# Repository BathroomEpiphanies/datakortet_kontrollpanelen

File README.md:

# datakortet_kontrollpanelen
Källkod för datakortets kontrollpanelen

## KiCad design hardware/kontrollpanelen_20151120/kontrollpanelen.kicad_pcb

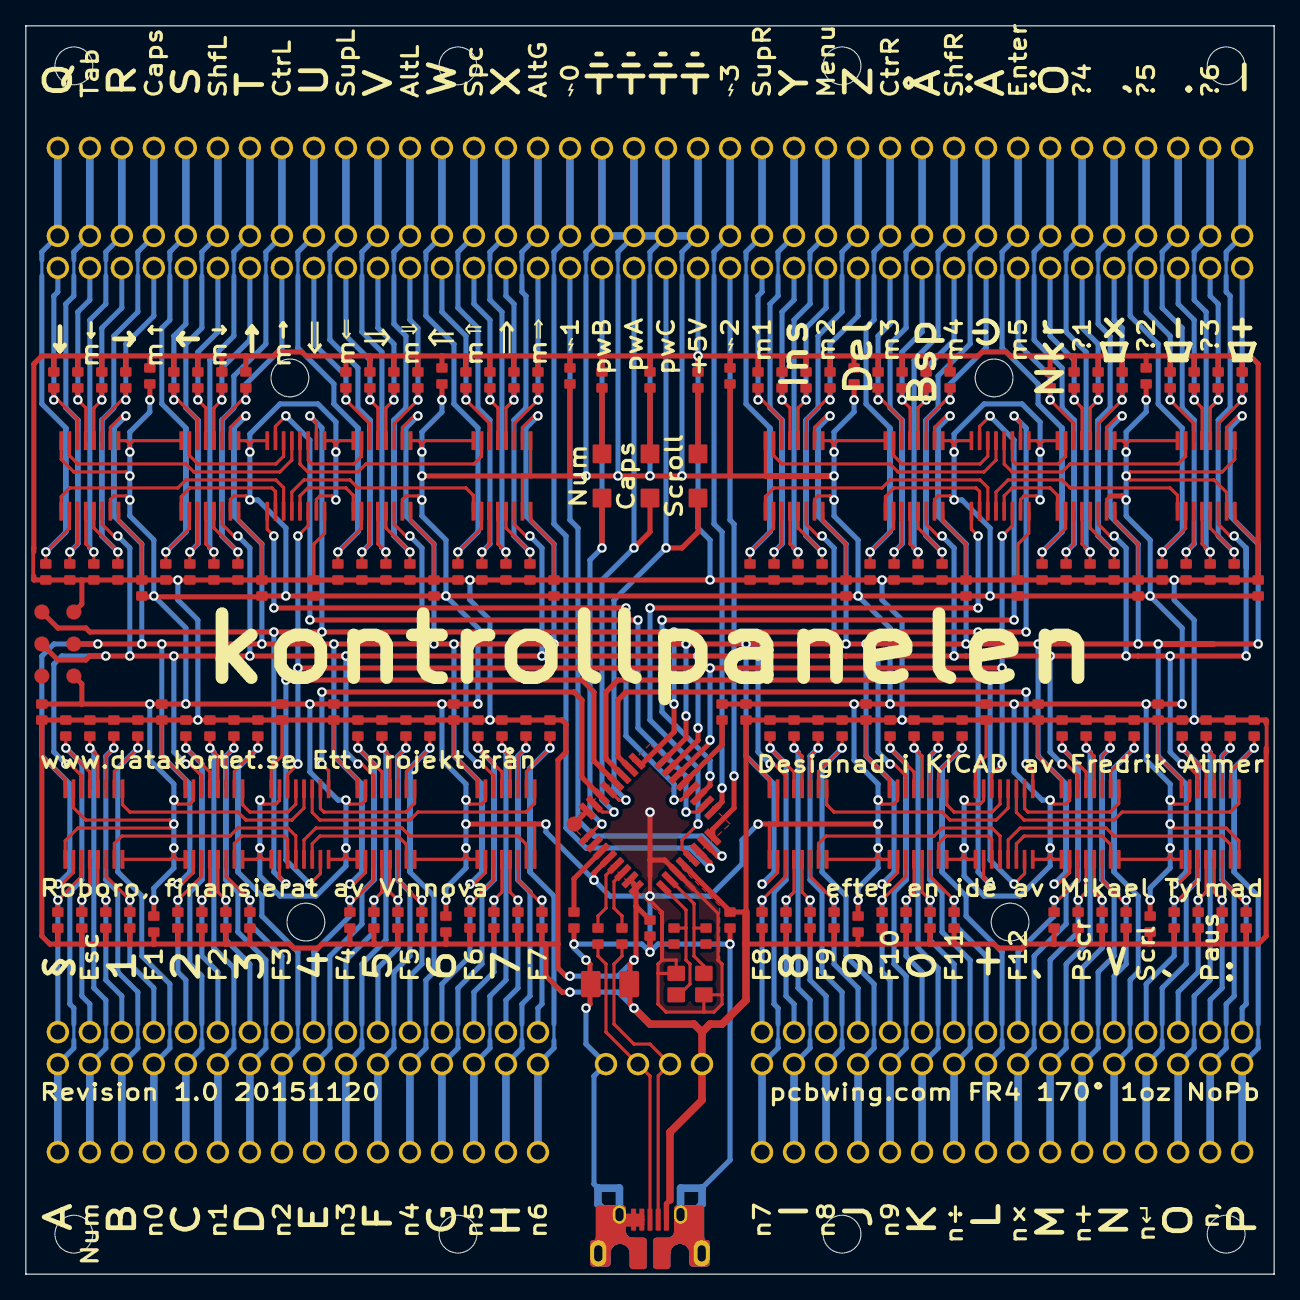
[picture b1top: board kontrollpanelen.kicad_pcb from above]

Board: 2 copper layers, 99.1 x 99.1 mm, 204 parts (0 on the bottom side), 192 nets.

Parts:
ANY1: ANYTHING; Kontrollpanelen
C1, C2, C3, C4, C5, C6, C7, C8, C9, C10, C11, C12, C13, C14, C15, C16, C17, C18, C19, C20, C301, C302, C303, C304, C305, C306, C307, C308, C309, C310: 0.1µ; Resistor_0603_-_Panasonic_ERJ
C21, C204: 1µF; Resistor_0603_-_Panasonic_ERJ
C201: 0.1µF; Resistor_0603_-_Panasonic_ERJ
C202, C203: 18pF; Resistor_0603_-_Panasonic_ERJ
C205: 10μF; Capacitor_1206_-_Vishay
D201, D202, D203: LED; LED_32x16mm_-_Avago_HSMx-C150
J1, J2, J3, J4: Terminal; Screw_Terminal_32
J5: USB_5; Connector_USBmicroB_inverted_-_FCI
J6: Terminal_12; Screw_Terminal_12
J7: ISP6; ISP_SMD_6
J8: USB_4; Screw_Terminal_4
R1, R2, R3, R4, R5, R6, R7, R8, R9, R10, R11, R12, R13, R14, R15, R16, R17, R18, R19, R20, R21, R22, R23, R24, R25, R26, R27, R28, R29, R30, R31, R32, R33, R34, R35, R36, R37, R38, R39, R40, R41, R42, R43, R44, R45, R46, R47, R48, R49, R50, R51, R52, R53, R54, R55, R56, R57, R58, R59, R60, R61, R62, R63, R64, R65, R66, R67, R68, R69, R70, R71, R72, R73, R74, R75, R76, R77, R78, R79, R80, R81, R82, R83, R84, R85, R86, R87, R88, R89, R90, R91, R92, R93, R94, R95, R96, R97, R98, R99, R100, R101, R102, R103, R104, R105, R106, R107, R108, R109, R110, R111, R112, R113, R114, R115, R116, R117, R118, R119, R120, R121, R122, R123, R124, R125, R126, R127, R128: 22MΩ; Resistor_0603_-_Panasonic_ERJ
R201, R204, R205, R206: 10kΩ; Resistor_0603_-_Panasonic_ERJ
R202, R203: 22Ω; Resistor_0603_-_Panasonic_ERJ
U1, U2, U3, U4, U5, U6, U7, U8, U9, U10, U11, U12, U13, U14, U15, U16, U17, U18, U19, U20: 74HC153; TSSOP16_-_Texas_Instruments
U201: ATMEGA32U2; TQFP32_-_Atmel
X201: 16MHz; Crystal_32x25mm_-_Abracon_ABM10

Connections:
/INT0: J6.1, U201.6
/INT1: J6.2, U201.7
/INT2: J6.12, U201.8
/INT3: J6.11, U201.9
/PWMA: J6.6, U201.23
/PWMB: J6.4, U201.25
/PWMC: J6.8, U201.21
/S0: J7.3, U1.14, U2.14, U3.14, U4.14, U5.14, U6.14, U7.14, U8.14, U9.14, U10.14, U11.14, U12.14, U13.14, U14.14, U15.14, U16.14, U201.15
/S1: J7.4, U1.2, U2.2, U3.2, U4.2, U5.2, U6.2, U7.2, U8.2, U9.2, U10.2, U11.2, U12.2, U13.2, U14.2, U15.2, U16.2, U201.16
/S2: U17.14, U18.14, U19.14, U20.14, U201.14
/S3: J7.1, U17.2, U18.2, U19.2, U20.2, U201.17
/Y0: U19.9, U201.22
/Y1: U19.7, U201.20
/Y2: U20.9, U201.18
/Y3: U20.7, U201.19
/Y4: U18.9, U201.5
/Y5: U18.7, U201.11
/Y6: U17.9, U201.12
/Y7: U17.7, U201.10
GND: C1.2, C2.2, C3.2, C4.2, C5.2, C6.2, C7.2, C8.2, C9.2, C10.2, C11.2, C12.2, C13.2, C14.2, C15.2, C16.2, C17.2, C18.2, C19.2, C20.2, C21.2, C201.2, C202.2, C203.2, C204.2, C205.2, C301.2, C302.2, C303.2, C304.2, C305.2, C306.2, C307.2, C308.2, C309.2, C310.2, J5.4, J5.5, J6.3, J6.5, J6.7, J6.9, J7.6, J8.4, R201.2, U1.1, U1.8, U1.15, U2.1, U2.8, U2.15, U3.1, U3.8, U3.15, U4.1, U4.8, U4.15, U5.1, U5.8, U5.15, U6.1, U6.8, U6.15, U7.1, U7.8, U7.15, U8.1, U8.8, U8.15, U9.1, U9.8, U9.15, U10.1, U10.8, U10.15, U11.1, U11.8, U11.15, U12.1, U12.8, U12.15, U13.1, U13.8, U13.15, U14.1, U14.8, U14.15, U15.1, U15.8, U15.15, U16.1, U16.8, U16.15, U17.1, U17.8, U17.15, U18.1, U18.8, U18.15, U19.1, U19.8, U19.15, U20.1, U20.8, U20.15, U201.3, U201.28, X201.2, X201.4
unnamed: C21.1, U201.27
unnamed: C202.1, U201.2, X201.3
unnamed: C203.1, U201.1, X201.1
unnamed: D201.1, R204.1
unnamed: D202.1, R205.1
unnamed: D203.1, R206.1
unnamed: J1.1, R33.1, U1.10
unnamed: J1.2, R1.1, U1.6
unnamed: J1.3, R34.1, U1.11
unnamed: J1.4, R2.1, U1.5
unnamed: J1.5, R35.1, U1.12
unnamed: J1.6, R3.1, U1.4
unnamed: J1.7, R36.1, U1.13
unnamed: J1.8, R4.1, U1.3
unnamed: J1.9, R37.1, U2.10
unnamed: J1.10, R5.1, U2.6
unnamed: J1.11, R38.1, U2.11
unnamed: J1.12, R6.1, U2.5
unnamed: J1.13, R39.1, U2.12
unnamed: J1.14, R7.1, U2.4
unnamed: J1.15, R40.1, U2.13
unnamed: J1.16, R8.1, U2.3
unnamed: J1.17, R41.1, U3.10
unnamed: J1.18, R9.1, U3.6
unnamed: J1.19, R42.1, U3.11
unnamed: J1.20, R10.1, U3.5
unnamed: J1.21, R43.1, U3.12
unnamed: J1.22, R11.1, U3.4
unnamed: J1.23, R44.1, U3.13
unnamed: J1.24, R12.1, U3.3
unnamed: J1.25, R45.1, U4.10
unnamed: J1.26, R13.1, U4.6
unnamed: J1.27, R46.1, U4.11
unnamed: J1.28, R14.1, U4.5
unnamed: J1.29, R47.1, U4.12
unnamed: J1.30, R15.1, U4.4
unnamed: J1.31, R48.1, U4.13
unnamed: J1.32, R16.1, U4.3
unnamed: J2.1, R49.1, U5.10
unnamed: J2.2, R17.1, U5.6
unnamed: J2.3, R50.1, U5.11
unnamed: J2.4, R18.1, U5.5
unnamed: J2.5, R51.1, U5.12
unnamed: J2.6, R19.1, U5.4
unnamed: J2.7, R52.1, U5.13
unnamed: J2.8, R20.1, U5.3
unnamed: J2.9, R53.1, U6.10
unnamed: J2.10, R21.1, U6.6
unnamed: J2.11, R54.1, U6.11
unnamed: J2.12, R22.1, U6.5
unnamed: J2.13, R55.1, U6.12
unnamed: J2.14, R23.1, U6.4
unnamed: J2.15, R56.1, U6.13
unnamed: J2.16, R24.1, U6.3
unnamed: J2.17, R57.1, U7.10
unnamed: J2.18, R25.1, U7.6
unnamed: J2.19, R58.1, U7.11
unnamed: J2.20, R26.1, U7.5
unnamed: J2.21, R59.1, U7.12
unnamed: J2.22, R27.1, U7.4
unnamed: J2.23, R60.1, U7.13
unnamed: J2.24, R28.1, U7.3
unnamed: J2.25, R61.1, U8.10
unnamed: J2.26, R29.1, U8.6
unnamed: J2.27, R62.1, U8.11
unnamed: J2.28, R30.1, U8.5
unnamed: J2.29, R63.1, U8.12
unnamed: J2.30, R31.1, U8.4
unnamed: J2.31, R64.1, U8.13
unnamed: J2.32, R32.1, U8.3
unnamed: J3.1, R80.1, U12.10
unnamed: J3.2, R112.1, U12.6
unnamed: J3.3, R79.1, U12.11
unnamed: J3.4, R111.1, U12.5
unnamed: J3.5, R78.1, U12.12
unnamed: J3.6, R110.1, U12.4
unnamed: J3.7, R77.1, U12.13
unnamed: J3.8, R109.1, U12.3
unnamed: J3.9, R76.1, U11.10
unnamed: J3.10, R108.1, U11.6
unnamed: J3.11, R75.1, U11.11
unnamed: J3.12, R107.1, U11.5
unnamed: J3.13, R74.1, U11.12
unnamed: J3.14, R106.1, U11.4
unnamed: J3.15, R73.1, U11.13
unnamed: J3.16, R105.1, U11.3
unnamed: J3.17, R72.1, U10.10
unnamed: J3.18, R104.1, U10.6
unnamed: J3.19, R71.1, U10.11
unnamed: J3.20, R103.1, U10.5
unnamed: J3.21, R70.1, U10.12
unnamed: J3.22, R102.1, U10.4
unnamed: J3.23, R69.1, U10.13
unnamed: J3.24, R101.1, U10.3
unnamed: J3.25, R68.1, U9.10
unnamed: J3.26, R100.1, U9.6
unnamed: J3.27, R67.1, U9.11
unnamed: J3.28, R99.1, U9.5
unnamed: J3.29, R66.1, U9.12
unnamed: J3.30, R98.1, U9.4
unnamed: J3.31, R65.1, U9.13
unnamed: J3.32, R97.1, U9.3
unnamed: J4.1, R96.1, U16.10
unnamed: J4.2, R128.1, U16.6
unnamed: J4.3, R95.1, U16.11
unnamed: J4.4, R127.1, U16.5
unnamed: J4.5, R94.1, U16.12
unnamed: J4.6, R126.1, U16.4
unnamed: J4.7, R93.1, U16.13
unnamed: J4.8, R125.1, U16.3
unnamed: J4.9, R92.1, U15.10
unnamed: J4.10, R124.1, U15.6
unnamed: J4.11, R91.1, U15.11
unnamed: J4.12, R123.1, U15.5
unnamed: J4.13, R90.1, U15.12
unnamed: J4.14, R122.1, U15.4
unnamed: J4.15, R89.1, U15.13
unnamed: J4.16, R121.1, U15.3
unnamed: J4.17, R88.1, U14.10
unnamed: J4.18, R120.1, U14.6
unnamed: J4.19, R87.1, U14.11
unnamed: J4.20, R119.1, U14.5
unnamed: J4.21, R86.1, U14.12
unnamed: J4.22, R118.1, U14.4
unnamed: J4.23, R85.1, U14.13
unnamed: J4.24, R117.1, U14.3
unnamed: J4.25, R84.1, U13.10
unnamed: J4.26, R116.1, U13.6
unnamed: J4.27, R83.1, U13.11
unnamed: J4.28, R115.1, U13.5
unnamed: J4.29, R82.1, U13.12
unnamed: J4.30, R114.1, U13.4
unnamed: J4.31, R81.1, U13.13
unnamed: J4.32, R113.1, U13.3
unnamed: J5.2, J8.2, R202.1
unnamed: J5.3, J8.3, R203.1
unnamed: R201.1, U201.13
unnamed: R202.2, U201.30
unnamed: R203.2, U201.29
unnamed: U1.7, U17.5
unnamed: U1.9, U17.11
unnamed: U10.7, U19.3
unnamed: U10.9, U19.13
unnamed: U11.7, U19.6
unnamed: U11.9, U19.10
unnamed: U12.7, U19.5
unnamed: U12.9, U19.11
unnamed: U13.7, U20.4
unnamed: U13.9, U20.12
unnamed: U14.7, U20.3
unnamed: U14.9, U20.13
unnamed: U15.7, U20.6
unnamed: U15.9, U20.10
unnamed: U16.7, U20.5
unnamed: U16.9, U20.11
unnamed: U3.7, U17.3
unnamed: U4.7, U17.4
unnamed: U2.7, U17.6
unnamed: U2.9, U17.10
unnamed: U4.9, U17.12
unnamed: U3.9, U17.13
unnamed: U7.7, U18.3
unnamed: U8.7, U18.4
unnamed: U5.7, U18.5
unnamed: U6.7, U18.6
unnamed: U6.9, U18.10
unnamed: U5.9, U18.11
unnamed: U8.9, U18.12
unnamed: U7.9, U18.13
unnamed: U9.7, U19.4
unnamed: U9.9, U19.12
VCC: C1.1, C2.1, C3.1, C4.1, C5.1, C6.1, C7.1, C8.1, C9.1, C10.1, C11.1, C12.1, C13.1, C14.1, C15.1, C16.1, C17.1, C18.1, C19.1, C20.1, C201.1, C204.1, C205.1, C301.1, C302.1, C303.1, C304.1, C305.1, C306.1, C307.1, C308.1, C309.1, C310.1, J5.1, J6.10, J7.2, J8.1, R1.2, R2.2, R3.2, R4.2, R5.2, R6.2, R7.2, R8.2, R9.2, R10.2, R11.2, R12.2, R13.2, R14.2, R15.2, R16.2, R17.2, R18.2, R19.2, R20.2, R21.2, R22.2, R23.2, R24.2, R25.2, R26.2, R27.2, R28.2, R29.2, R30.2, R31.2, R32.2, R33.2, R34.2, R35.2, R36.2, R37.2, R38.2, R39.2, R40.2, R41.2, R42.2, R43.2, R44.2, R45.2, R46.2, R47.2, R48.2, R49.2, R50.2, R51.2, R52.2, R53.2, R54.2, R55.2, R56.2, R57.2, R58.2, R59.2, R60.2, R61.2, R62.2, R63.2, R64.2, R65.2, R66.2, R67.2, R68.2, R69.2, R70.2, R71.2, R72.2, R73.2, R74.2, R75.2, R76.2, R77.2, R78.2, R79.2, R80.2, R81.2, R82.2, R83.2, R84.2, R85.2, R86.2, R87.2, R88.2, R89.2, R90.2, R91.2, R92.2, R93.2, R94.2, R95.2, R96.2, R97.2, R98.2, R99.2, R100.2, R101.2, R102.2, R103.2, R104.2, R105.2, R106.2, R107.2, R108.2, R109.2, R110.2, R111.2, R112.2, R113.2, R114.2, R115.2, R116.2, R117.2, R118.2, R119.2, R120.2, R121.2, R122.2, R123.2, R124.2, R125.2, R126.2, R127.2, R128.2, R204.2, R205.2, R206.2, U1.16, U2.16, U3.16, U4.16, U5.16, U6.16, U7.16, U8.16, U9.16, U10.16, U11.16, U12.16, U13.16, U14.16, U15.16, U16.16, U17.16, U18.16, U19.16, U20.16, U201.4, U201.31, U201.32

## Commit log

2015-12-29 Fixade layouten.
2015-12-30 Fler knappar
2016-01-03 Tester
